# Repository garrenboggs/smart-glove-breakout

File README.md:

# smart-glove-breakout
Breakout PCB for the Smart Glove sign language recognition technology. Designed by team HandsOn.

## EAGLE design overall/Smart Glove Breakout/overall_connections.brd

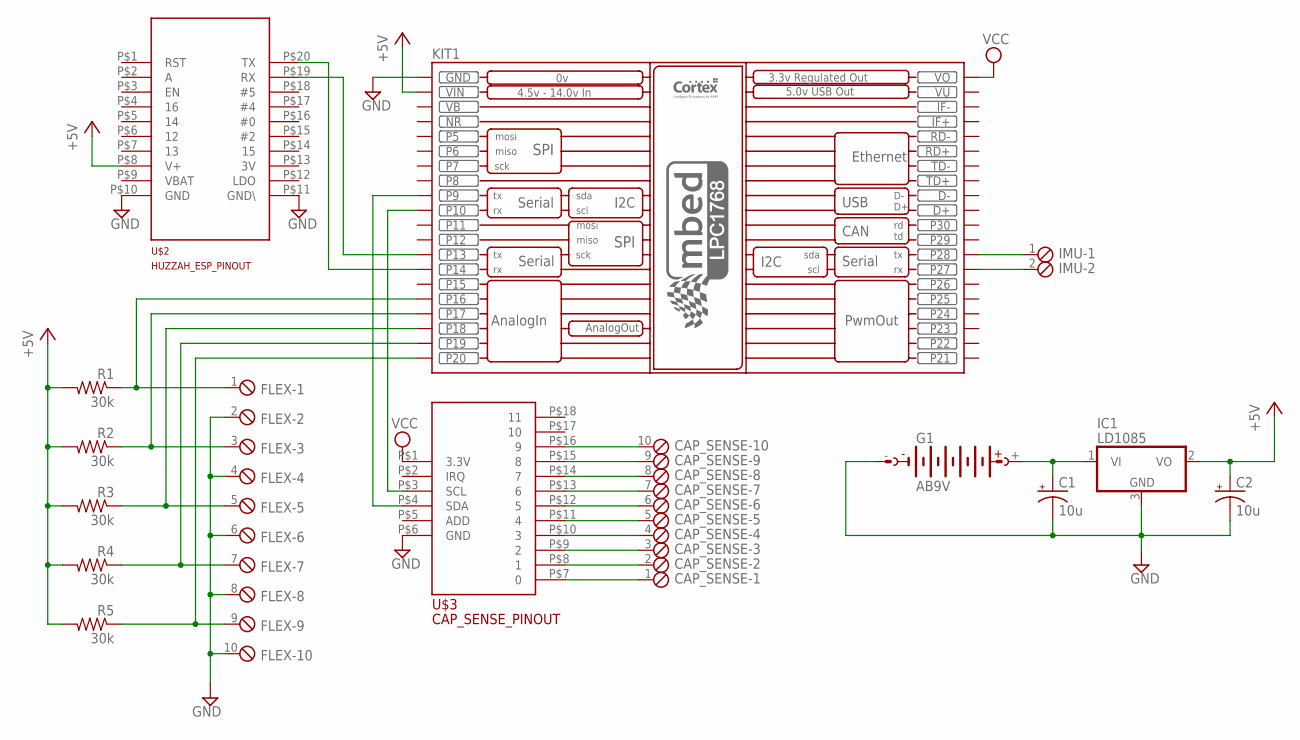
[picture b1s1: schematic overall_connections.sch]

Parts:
C1, C2: 10u; E1,8-4
CAP_SENSE: MPT10; 10POL254
FLEX: MPT10; 10POL254
G1: AB9V
IC1: LD1085; TO220H
IMU: MPT2; 2POL254
KIT1: MBED_NXP_LPC1768; MBED-KIT
R1, R2, R3, R4, R5: 30k; 0204/7
U$2: HUZZAH_ESP_PINOUT; DIP20
U$3: CAP_SENSE_PINOUT; DIP18

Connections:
+5V: C2.+, IC1.2 (VO), KIT1.VIN, R1.2, R2.2, R3.2, R4.2, R5.2, U$2.P$8 (V+)
FLEX1: FLEX.1, KIT1.P$16 (P16), R1.1
FLEX2: FLEX.3, KIT1.P$17 (P17), R2.1
FLEX3: FLEX.5, KIT1.P$18 (P18), R3.1
FLEX4: FLEX.7, KIT1.P$19 (P19), R4.1
FLEX5: FLEX.9, KIT1.P$20 (P20), R5.1
GND: C1.-, C2.-, FLEX.2, FLEX.4, FLEX.6, FLEX.8, FLEX.10, G1.-, IC1.3 (GND), KIT1.GND, U$2.P$10 (GND), U$2.P$11 (GND\), U$3.P$6 (GND)
unnamed: KIT1.P$14 (P14), U$2.P$20 (TX)
unnamed: KIT1.P$13 (P13), U$2.P$19 (RX)
unnamed: KIT1.P$9 (P9), U$3.P$4 (SDA)
unnamed: KIT1.P$10 (P10), U$3.P$3 (SCL)
unnamed: IMU.2, KIT1.P$27 (P27)
unnamed: IMU.1, KIT1.P$28 (P28)
unnamed: C1.+, G1.+, IC1.1 (VI)
unnamed: CAP_SENSE.1, U$3.P$7 (0)
unnamed: CAP_SENSE.2, U$3.P$8 (1)
unnamed: CAP_SENSE.3, U$3.P$9 (2)
unnamed: CAP_SENSE.4, U$3.P$10 (3)
unnamed: CAP_SENSE.5, U$3.P$11 (4)
unnamed: CAP_SENSE.6, U$3.P$12 (5)
unnamed: CAP_SENSE.7, U$3.P$13 (6)
unnamed: CAP_SENSE.8, U$3.P$14 (7)
unnamed: CAP_SENSE.9, U$3.P$15 (8)
unnamed: CAP_SENSE.10, U$3.P$16 (9)
NR: KIT1.NR
VB: KIT1.VB
VCC: KIT1.VOUT (VO), U$3.P$1 (3.3V)
VU: KIT1.VU

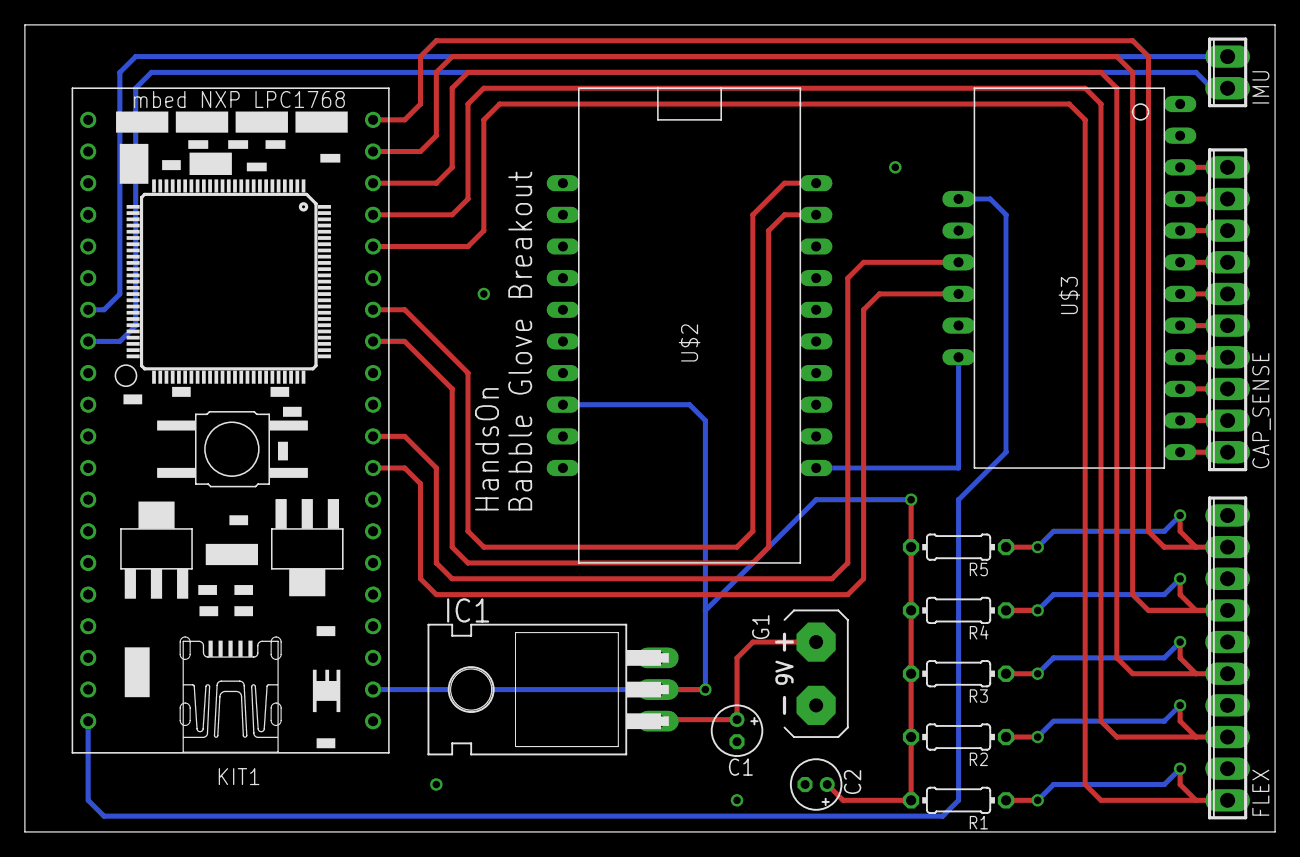
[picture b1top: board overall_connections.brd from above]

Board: 2 copper layers, 100.3 x 64.8 mm, 15 parts (0 on the bottom side), 25 nets.

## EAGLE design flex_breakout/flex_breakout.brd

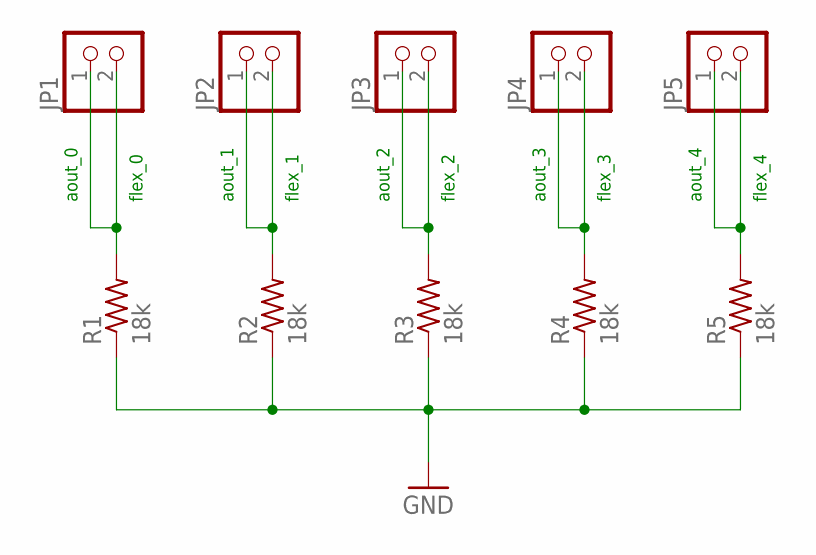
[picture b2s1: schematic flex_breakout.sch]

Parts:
JP1, JP2, JP3, JP4, JP5: PINHD-1X2; 1X02
R1, R2, R3, R4, R5: 18k; 0204/7

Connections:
GND: R1.1, R2.1, R3.1, R4.1, R5.1
unnamed: JP1.1, JP1.2, R1.2
unnamed: JP2.1, JP2.2, R2.2
unnamed: JP3.1, JP3.2, R3.2
unnamed: JP4.1, JP4.2, R4.2
unnamed: JP5.1, JP5.2, R5.2

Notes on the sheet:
aout_0
aout_1
aout_2
aout_3
aout_4
flex_0
flex_1
flex_2
flex_3
flex_4

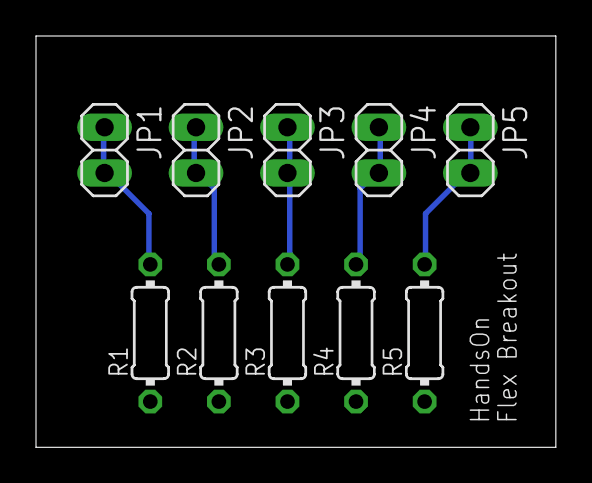
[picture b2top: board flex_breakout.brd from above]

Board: 2 copper layers, 28.9 x 22.9 mm, 10 parts (0 on the bottom side), 6 nets.

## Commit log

2016-03-06 Flex Sensor Breakout Board
    Eagle schematics for the Smart Glove flex sensor breakout board. This
    breakout board provides a resistive voltage divider for the glove's five
    flex sensors. Two-pin jumpers are attached to allow connections to be
    made, one to the flex sensor as an input, and the other as an analog
    output voltage to be read by the mbed's AnalogIn pins.
2016-03-08 Created Library for IC Pinouts
    Created a new library for Eagle device schematics in order to simplify
    setting up pin connections for the breakout board.
    The schematic block diagram for the mbed developer pinouts have been
    created and added to this library.
2016-03-08 Updated Library of IC pinouts
    Includes the pinouts for the MPR121 Capacitive Touch Sensor breakout
    board and the Huzzah ESP breakout board.
2016-03-10 Started Board File
    Using new mbed part from lib found online, started board file with some
    obvious traces added.
2016-03-15 Revert "Started Board File"
    This reverts commit 9f60d38fc5464a5e955318b8b377fab6b9ea1dbb.
2016-03-15 Re-Do Of Basic Set Up
    Data loss on the initial commit, restored.
2016-03-15 Prevent merge conflict
    Committing file to prevent merge conflict with other branches.
2016-03-17 Revised PCB design
    Fixed error with voltage regulator pinout, package pins for our device
    did not match the Eagle schematic. Also routed V+ pins to both the mbed
    device and the Huzzah IC.
